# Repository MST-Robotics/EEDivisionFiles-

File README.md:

# Robotics Design Team
## Electrical Divison Files

This is a place to store all EE divison files like board files and such

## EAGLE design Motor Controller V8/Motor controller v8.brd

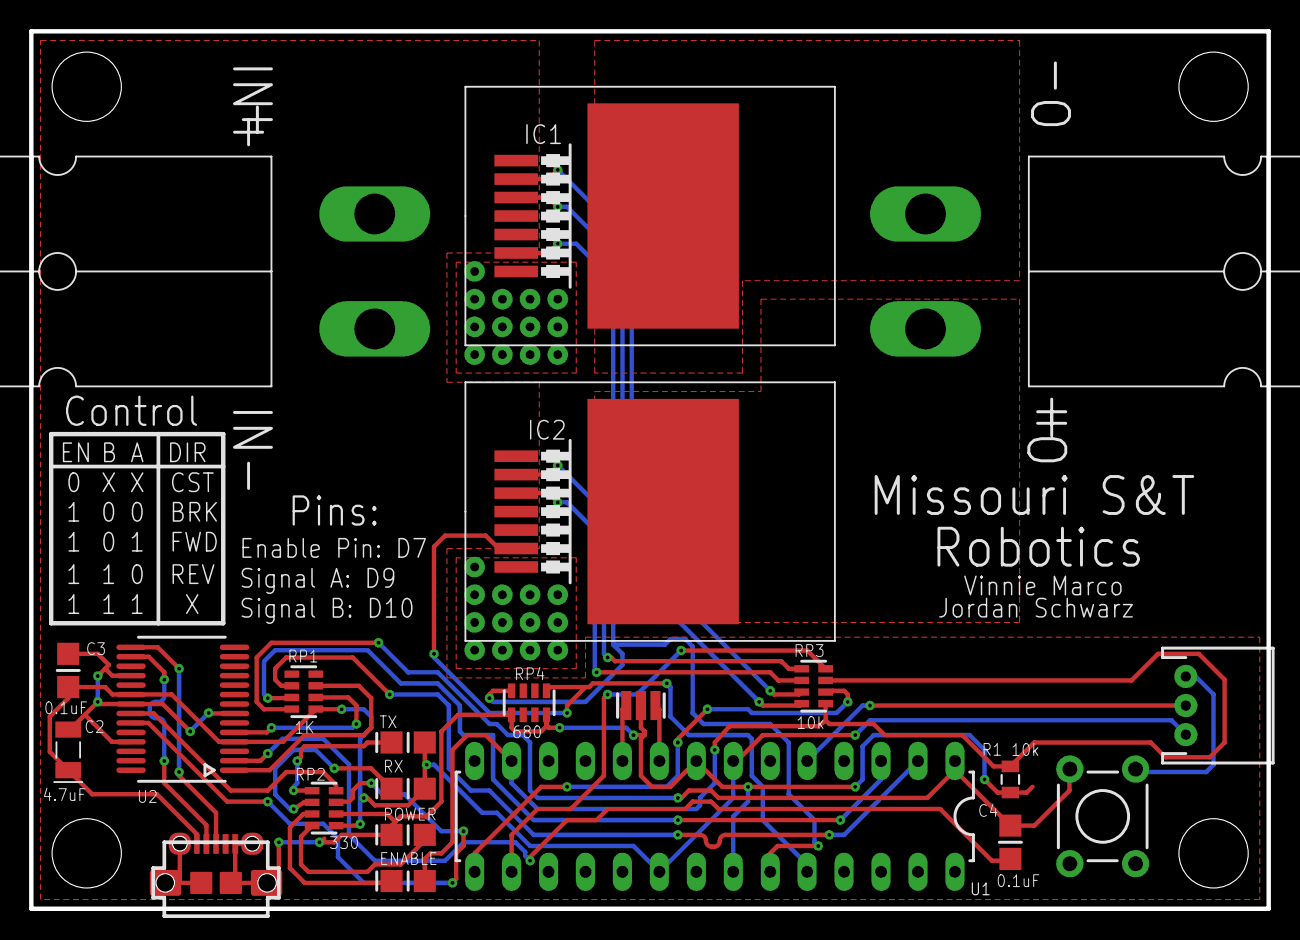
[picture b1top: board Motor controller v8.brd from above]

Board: 2 copper layers, 85.1 x 60.3 mm, 22 parts (0 on the bottom side), 31 nets.

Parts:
C2: 4.7uF; TAN-A
C3, C4: 0.1uF; CAP0805-NP
IC1, IC2: TLE5205-2G; P-TO263-7-1
J2, J3: POWERPOLE_POWER25A_HORIZONTAL_G2; POWERPOLE_PAIR_25A_HORIZ_G2
JP1: JST-3-PTH
LED1: RED_RX; LED0805
LED2: GREEN_TX; LED0805
LED3: GREEN; LED0805
LED4: BLUE; LED0805
R1: 10k; 0805
RP1: 1K; RES4NT
RP2: 330; RES4NT
RP3: 10k; RES4NT
RP4: 680; RES4NT
S1: SWITCH-MOMENTARY-2PTH; TACTILE-PTH
U1: ATMEGA328P_PDIP; DIL28-3
U2: FT232RL; SSOP28
U$8: USB; CON2_USB_MICRO_B_AT
Y1: 16MHz; RESONATOR

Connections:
+5V: C2.1, C3.1, JP1.3, LED1.2, LED2.2, RP1.5, RP2.1, U1.7, U1.20, U2.4, U2.20, U$8.P1
A0: IC1.6, RP4.8, U1.23
A1: IC2.6, RP4.5, U1.24
D0/RX: RP1.2, U1.2
D1/TX: RP1.3, U1.3
D3: JP1.2, U1.5
D7: LED3.2, R1.2, RP3.1, RP3.3, U1.13
D9: RP3.2, U1.15
D10: RP3.4, U1.16
GND: C2.2, C3.2, IC1.1, IC1.5, IC2.1, IC2.5, J3.BLACK, JP1.1, LED4.1, R1.1, RP2.2, RP4.1, RP4.4, S1.1, U1.8, U1.22, U2.7, U2.18, U2.21, U2.25, U$8.P5, U$8.S1, U$8.S2, U$8.S3, U$8.S4, U$8.S5, U$8.S6, Y1.2
unnamed: U1.9, Y1.1
unnamed: U1.10, Y1.3
unnamed: LED4.2, RP2.8
unnamed: C4.2, U2.2
unnamed: U2.15, U$8.P3
unnamed: U2.16, U$8.P2
unnamed: RP2.3, U2.23
unnamed: RP2.4, U2.22
unnamed: LED1.1, RP2.6
unnamed: LED2.1, RP2.5
unnamed: LED3.1, RP2.7
unnamed: IC1.3, RP3.8
unnamed: IC2.3, RP3.6
unnamed: IC1.2, RP3.7
unnamed: IC2.2, RP3.5
unnamed: IC1.8, J2.BLACK
unnamed: IC2.8, J2.RED
RESET: C4.1, RP1.4, S1.3, U1.1
RX: RP1.7, U2.1
TX: RP1.6, U2.5
VCC: IC1.7, IC2.7, J3.RED

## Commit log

2016-10-06 Uploaded Most Recent Motor Controller Design
2016-10-13 Add libraries used in the BMS/E-stop system
2016-10-13 Unnecessary backup file

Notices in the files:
parts and their libraries:
SparkFun-Connectors: Licensing: Creative Commons ShareAlike 4.0 International - https://creativecommons.org/licenses/by-sa/4.0
